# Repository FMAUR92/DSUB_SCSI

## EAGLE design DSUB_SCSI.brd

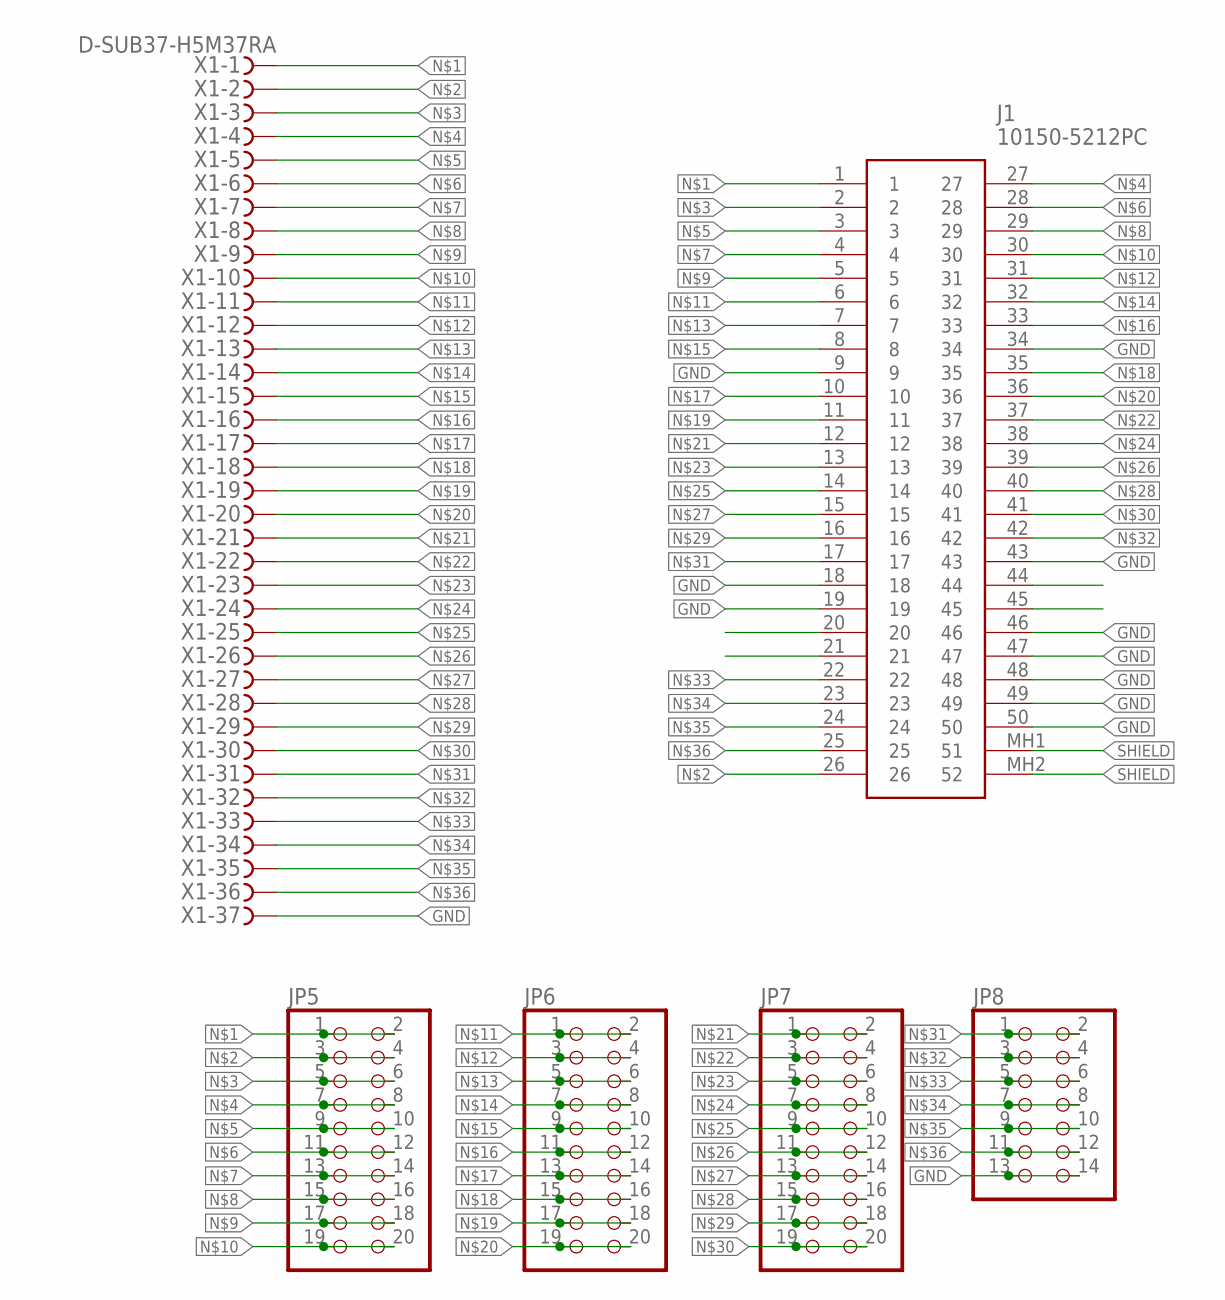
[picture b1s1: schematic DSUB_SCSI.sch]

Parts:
J1: 10150-5212PC; 101505212PC
JP5, JP6, JP7: PINHD-2X10; 2X10
JP8: PINHD-2X7; 2X07
X1: D-SUB37-H5M37RA; H5M37RA

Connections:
GND: J1.9, J1.18, J1.19, J1.34, J1.43, J1.46, J1.47, J1.48, J1.49, J1.50, JP8.13, JP8.14, X1.37
unnamed: J1.1, JP5.1, JP5.2, X1.1
unnamed: J1.26, JP5.3, JP5.4, X1.2
unnamed: J1.2, JP5.5, JP5.6, X1.3
unnamed: J1.27, JP5.7, JP5.8, X1.4
unnamed: J1.3, JP5.9, JP5.10, X1.5
unnamed: J1.28, JP5.11, JP5.12, X1.6
unnamed: J1.4, JP5.13, JP5.14, X1.7
unnamed: J1.29, JP5.15, JP5.16, X1.8
unnamed: J1.5, JP5.17, JP5.18, X1.9
unnamed: J1.30, JP5.19, JP5.20, X1.10
unnamed: J1.6, JP6.1, JP6.2, X1.11
unnamed: J1.31, JP6.3, JP6.4, X1.12
unnamed: J1.7, JP6.5, JP6.6, X1.13
unnamed: J1.32, JP6.7, JP6.8, X1.14
unnamed: J1.8, JP6.9, JP6.10, X1.15
unnamed: J1.33, JP6.11, JP6.12, X1.16
unnamed: J1.10, JP6.13, JP6.14, X1.17
unnamed: J1.35, JP6.15, JP6.16, X1.18
unnamed: J1.11, JP6.17, JP6.18, X1.19
unnamed: J1.36, JP6.19, JP6.20, X1.20
unnamed: J1.12, JP7.1, JP7.2, X1.21
unnamed: J1.37, JP7.3, JP7.4, X1.22
unnamed: J1.13, JP7.5, JP7.6, X1.23
unnamed: J1.38, JP7.7, JP7.8, X1.24
unnamed: J1.14, JP7.9, JP7.10, X1.25
unnamed: J1.39, JP7.11, JP7.12, X1.26
unnamed: J1.15, JP7.13, JP7.14, X1.27
unnamed: J1.40, JP7.15, JP7.16, X1.28
unnamed: J1.16, JP7.17, JP7.18, X1.29
unnamed: J1.41, JP7.19, JP7.20, X1.30
unnamed: J1.17, JP8.1, JP8.2, X1.31
unnamed: J1.42, JP8.3, JP8.4, X1.32
unnamed: J1.22, JP8.5, JP8.6, X1.33
unnamed: J1.23, JP8.7, JP8.8, X1.34
unnamed: J1.24, JP8.9, JP8.10, X1.35
unnamed: J1.25, JP8.11, JP8.12, X1.36
SHIELD: J1.MH1 (51), J1.MH2 (52)

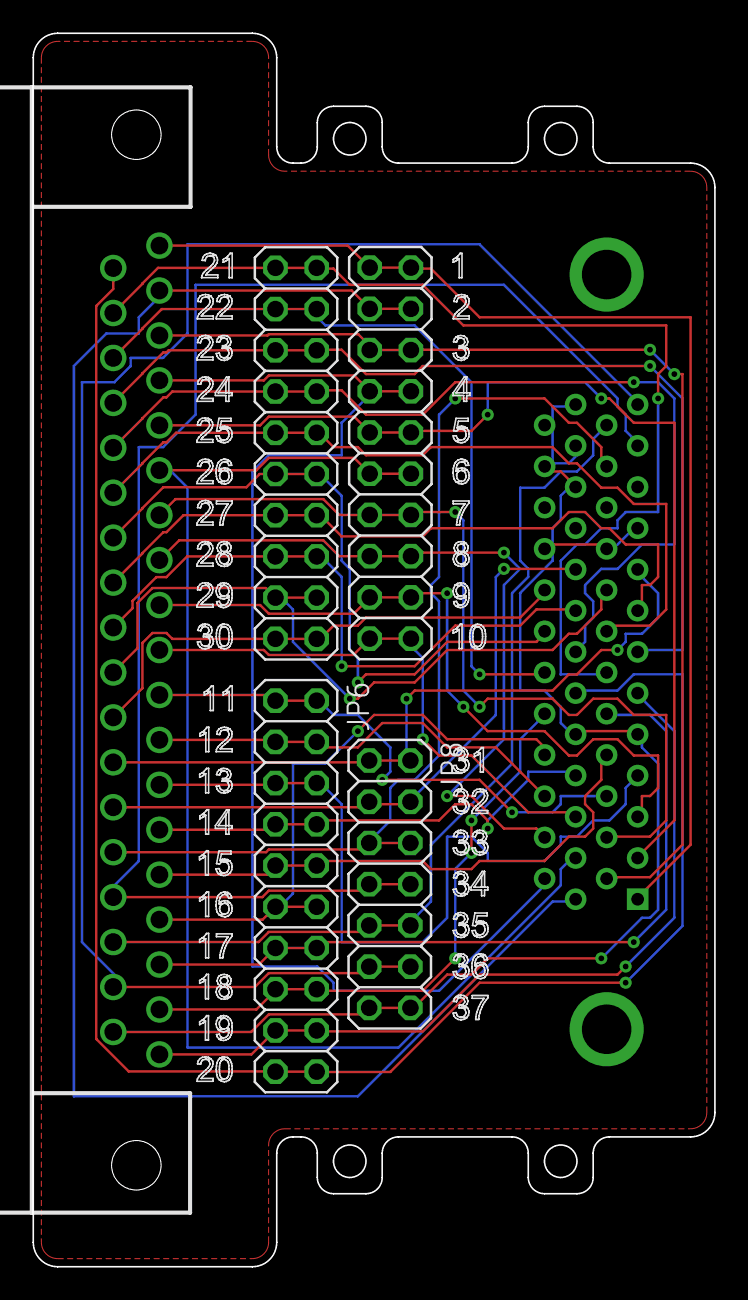
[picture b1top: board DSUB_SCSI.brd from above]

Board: 2 copper layers, 42.0 x 76.0 mm, 6 parts (1 on the bottom side), 38 nets.

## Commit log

2023-02-23 Updated brd file
2023-03-10 Updated board and schematic
    Fixed footprint for SCSI connector, and doubled the number of test pins.
2023-03-10 Updated case dwg file
    Modified closure mechanism, and increased size of hole to access additional test pins.
